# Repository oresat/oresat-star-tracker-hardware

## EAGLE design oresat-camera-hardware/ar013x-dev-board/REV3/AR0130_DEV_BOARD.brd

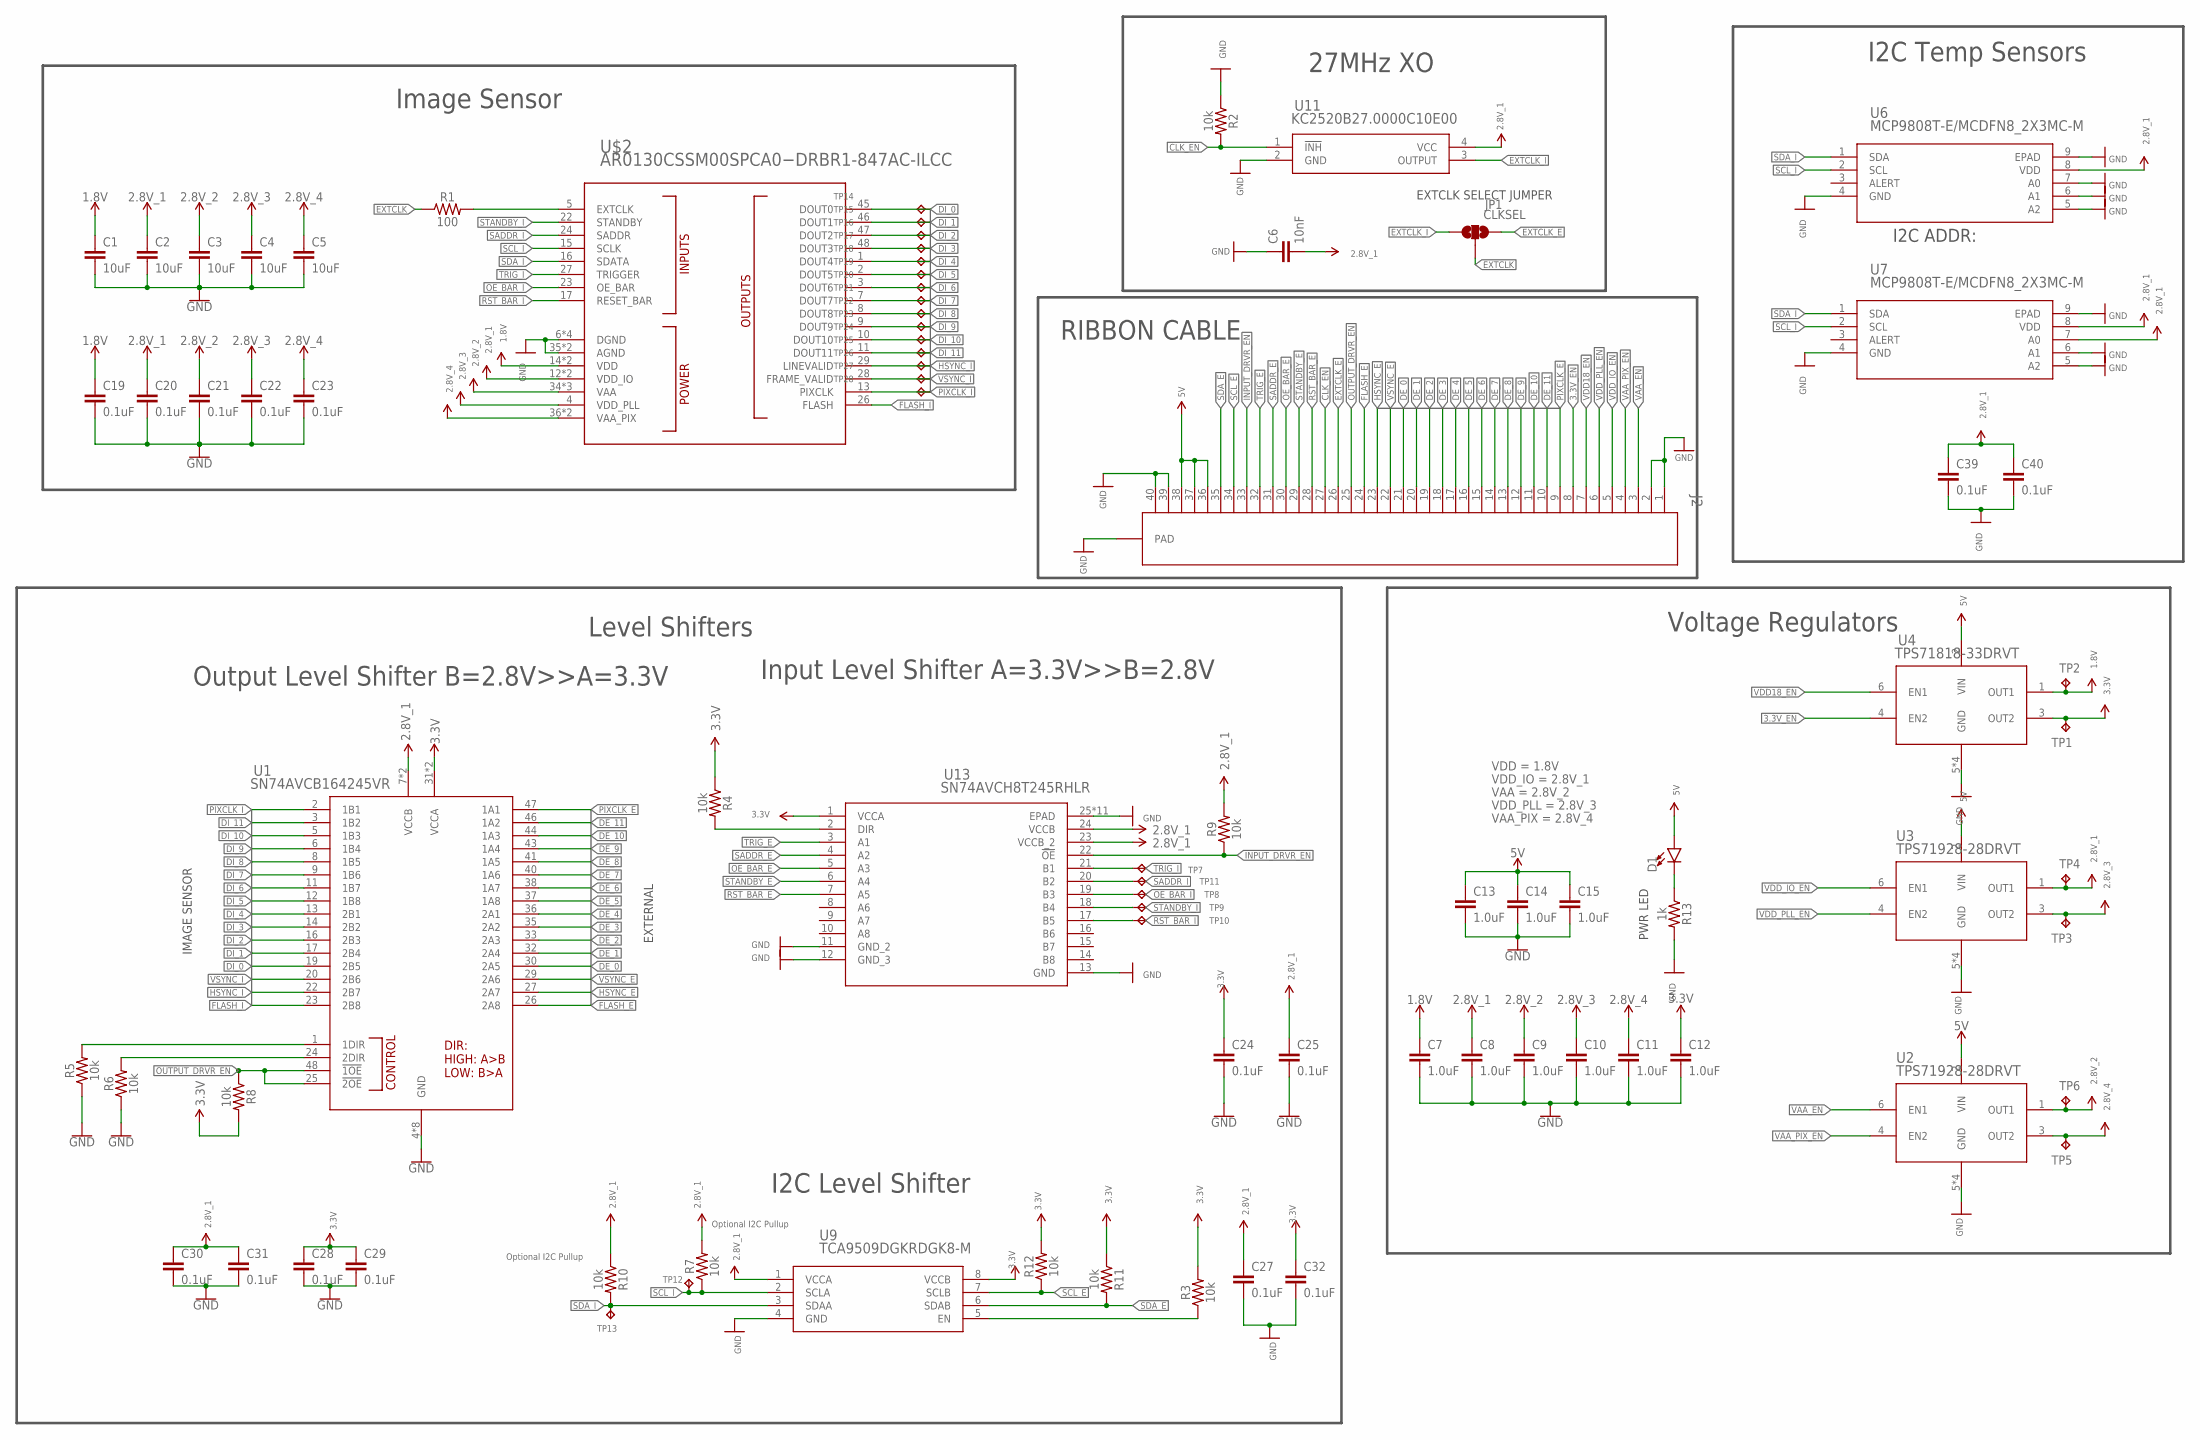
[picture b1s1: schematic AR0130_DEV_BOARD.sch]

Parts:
C1, C2, C3, C4, C5: 10uF; 0603
C6: 10nF; 0402
C7, C8, C9, C10, C11, C12, C13, C14, C15: 1.0uF; 0402
C19, C20, C21, C22, C23, C24, C25, C27, C28, C29, C30, C31, C32, C39, C40: 0.1uF; 0402
D1: LED0603; LED-0603
J2: 4-1734592-04-1734592-0; TE_4-1734592-0
JP1: CLKSEL; SJ_3_PASTE1&2
R1: 100; 0402
R2, R3, R4, R5, R6, R7, R8, R9, R10, R11, R12: 10k; 0402
R13: 1k; 0402
TP1, TP2, TP3, TP4, TP5, TP6, TP7, TP8, TP9, TP10, TP11, TP12, TP13, TP14, TP15, TP16, TP17, TP18, TP19, TP20, TP21, TP22, TP23, TP24, TP25, TP26, TP27, TP28: TPTP06R; TP06R
U1: SN74AVCB164245VR; DGV48
U2, U3: TPS71928-28DRVT; DRV6_1P6X1
U4: TPS71818-33DRVT; DRV6_1P6X1
U6, U7: MCP9808T-E/MCDFN8_2X3MC-M; DFN8_2X3MC-M
U9: TCA9509DGKRDGK8-M; DGK8-M
U11: KC2520B27.0000C10E00; OSC_KYOCERA_KC2520B
U13: SN74AVCH8T245RHLR; RHL24_4P05X2P05
U$2: AR0130CSSM00SPCA0−DRBR1-847AC-ILCC; AR0130CSSM00SPCA0−DRBR1-847AB

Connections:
1.8V: C1.1, C7.1, C19.1, TP2.TP, U4.1 (OUT1), U$2.14 (VDD), U$2.19 (VDD); also elsewhere on the board
3.3V: C12.1, C24.1, C28.1, C29.1, C32.1, R3.2, R4.1, R8.2, R11.1, R12.2, TP1.TP, U1.31 (VCCA), U4.3 (OUT2), U9.8 (VCCB), U13.1 (VCCA); also elsewhere on the board
3.3V_EN: J2.8, U4.4 (EN2); also elsewhere on the board
5V: C13.1, C14.1, C15.1, D1.A, J2.36, J2.37, J2.38, U2.2 (VIN), U3.2 (VIN), U4.2 (VIN); also elsewhere on the board
CLK_EN: J2.27, R2.2, U11.1 (!INH)
DE_0: J2.21, U1.30 (2A5); also elsewhere on the board
DE_1: J2.20, U1.32 (2A4); also elsewhere on the board
DE_2: J2.19, U1.33 (2A3); also elsewhere on the board
DE_3: J2.18, U1.35 (2A2); also elsewhere on the board
DE_4: J2.17, U1.36 (2A1); also elsewhere on the board
DE_5: J2.16, U1.37 (1A8); also elsewhere on the board
DE_6: J2.15, U1.38 (1A7); also elsewhere on the board
DE_7: J2.14, U1.40 (1A6); also elsewhere on the board
DE_8: J2.13, U1.41 (1A5); also elsewhere on the board
DE_9: J2.12, U1.43 (1A4); also elsewhere on the board
DE_10: J2.11, U1.44 (1A3); also elsewhere on the board
DE_11: J2.10, U1.46 (1A2); also elsewhere on the board
DI_0: TP14.TP, U1.19 (2B5), U$2.45 (DOUT0); also elsewhere on the board
DI_1: TP15.TP, U1.17 (2B4), U$2.46 (DOUT1); also elsewhere on the board
DI_2: TP16.TP, U1.16 (2B3), U$2.47 (DOUT2); also elsewhere on the board
DI_3: TP17.TP, U1.14 (2B2), U$2.48 (DOUT3); also elsewhere on the board
DI_4: TP18.TP, U1.13 (2B1), U$2.1 (DOUT4); also elsewhere on the board
DI_5: TP19.TP, U1.12 (1B8), U$2.2 (DOUT5); also elsewhere on the board
DI_6: TP20.TP, U1.11 (1B7), U$2.3 (DOUT6); also elsewhere on the board
DI_7: TP21.TP, U1.9 (1B6), U$2.7 (DOUT7); also elsewhere on the board
DI_8: TP22.TP, U1.8 (1B5), U$2.8 (DOUT8); also elsewhere on the board
DI_9: TP23.TP, U1.6 (1B4), U$2.9 (DOUT9); also elsewhere on the board
DI_10: TP24.TP, U1.5 (1B3), U$2.10 (DOUT10); also elsewhere on the board
DI_11: TP25.TP, U1.3 (1B2), U$2.11 (DOUT11); also elsewhere on the board
EXTCLK: JP1.2, R1.1
EXTCLK_E: J2.26, JP1.3
EXTCLK_I: JP1.1, U11.3 (OUTPUT)
FLASH_E: J2.24, U1.26 (2A8); also elsewhere on the board
FLASH_I: U1.23 (2B8), U$2.26 (FLASH); also elsewhere on the board
HSYNC_E: J2.23, U1.27 (2A7); also elsewhere on the board
HSYNC_I: TP26.TP, U1.22 (2B7), U$2.29 (LINEVALID); also elsewhere on the board
INPUT_DRVR_EN: J2.33, R9.1, U13.22 (!OE)
unnamed: R1.2, U$2.5 (EXTCLK)
unnamed: D1.C, R13.1
unnamed 39: R5.2, U1.1 (1DIR); also elsewhere on the board
unnamed: R3.1, U9.5 (EN)
unnamed: R4.2, U13.2 (DIR)
unnamed 42: R6.2, U1.24 (2DIR); also elsewhere on the board
OE_BAR_E: J2.30, U13.5 (A3)
OE_BAR_I: TP8.TP, U13.19 (B3), U$2.23 (OE_BAR)
OUTPUT_DRVR_EN: J2.25, R8.1, U1.25 (!2OE), U1.48 (!1OE); also elsewhere on the board
PIXCLK_E: J2.9, U1.47 (1A1); also elsewhere on the board
PIXCLK_I: TP28.TP, U1.2 (1B1), U$2.13 (PIXCLK); also elsewhere on the board
RST_BAR_E: J2.28, U13.7 (A5)
RST_BAR_I: TP9.TP, U13.17 (B5), U$2.17 (RESET_BAR)
SADDR_E: J2.31, U13.4 (A2)
SADDR_I: TP11.TP, U13.20 (B2), U$2.24 (SADDR)
SCL_E: J2.34, R12.1, U9.7 (SCLB)
SCL_I: R7.1, TP12.TP, U6.2 (SCL), U7.2 (SCL), U9.2 (SCLA), U$2.15 (SCLK)
SDA_E: J2.35, R11.2, U9.6 (SDAB)
SDA_I: R10.2, TP13.TP, U6.1 (SDA), U7.1 (SDA), U9.3 (SDAA), U$2.16 (SDATA)
STANDBY_E: J2.29, U13.6 (A4)
STANDBY_I: TP10.TP, U13.18 (B4), U$2.22 (STANDBY)
TRIG_E: J2.32, U13.3 (A1)
TRIG_I: TP7.TP, U13.21 (B1), U$2.27 (TRIGGER)
VAA_EN: J2.3, U2.6 (EN1); also elsewhere on the board
VAA_PIX_EN: J2.4, U2.4 (EN2); also elsewhere on the board
VCC: C3.1, C9.1, C21.1, TP6.TP, U2.1 (OUT1), U$2.34 (VAA), U$2.38 (VAA), U$2.40 (VAA); also elsewhere on the board
VCC_1: C4.1, C10.1, C22.1, TP3.TP, U3.3 (OUT2), U$2.4 (VDD_PLL); also elsewhere on the board
VCC_2: C5.1, C11.1, C23.1, TP5.TP, U2.3 (OUT2), U$2.36 (VAA_PIX), U$2.37 (VAA_PIX); also elsewhere on the board
VDD18_EN: J2.7, U4.6 (EN1); also elsewhere on the board
VDD_IO_EN: J2.5, U3.6 (EN1); also elsewhere on the board
VDD_PLL_EN: J2.6, U3.4 (EN2); also elsewhere on the board
VSYNC_E: J2.22, U1.29 (2A6); also elsewhere on the board
VSYNC_I: TP27.TP, U1.20 (2B6), U$2.28 (FRAME_VALID); also elsewhere on the board

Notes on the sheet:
I2C Temp Sensors
I2C Level Shifter
Voltage Regulators
Image Sensor
Output Level Shifter B=2.8V>>A=3.3V
27MHz XO
Input Level Shifter A=3.3V>>B=2.8V
Level Shifters
VDD_IO = 2.8V_1
Optional I2C Pullup
VDD = 1.8V
VDD_PLL = 2.8V_3
VAA = 2.8V_2
VAA_PIX = 2.8V_4
EXTCLK SELECT JUMPER
RIBBON CABLE
IMAGE SENSOR
EXTERNAL
PWR LED
I2C ADDR:

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
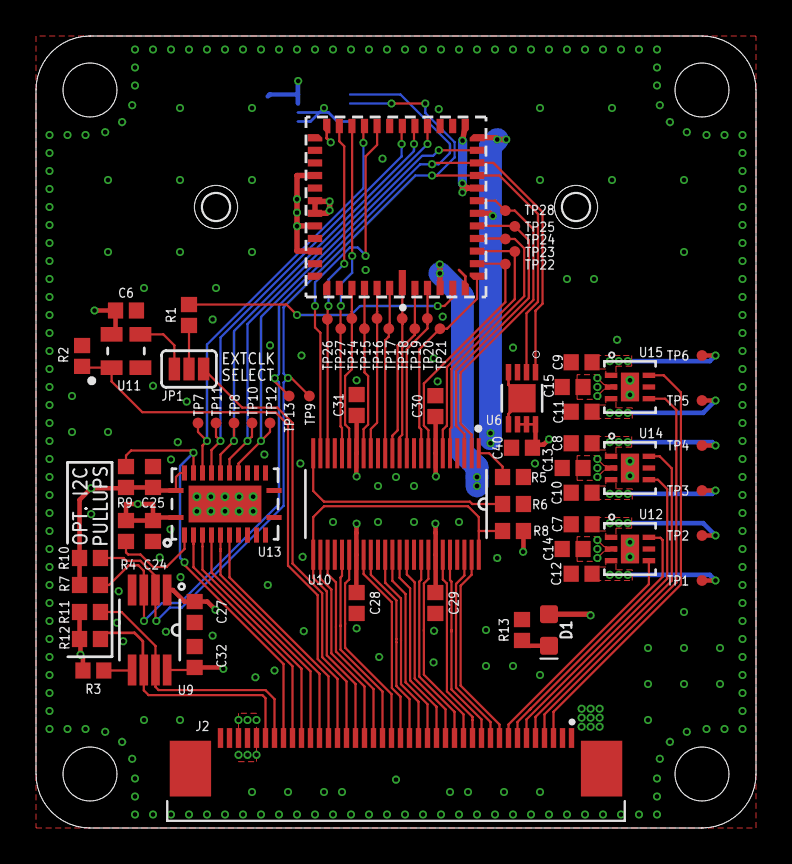
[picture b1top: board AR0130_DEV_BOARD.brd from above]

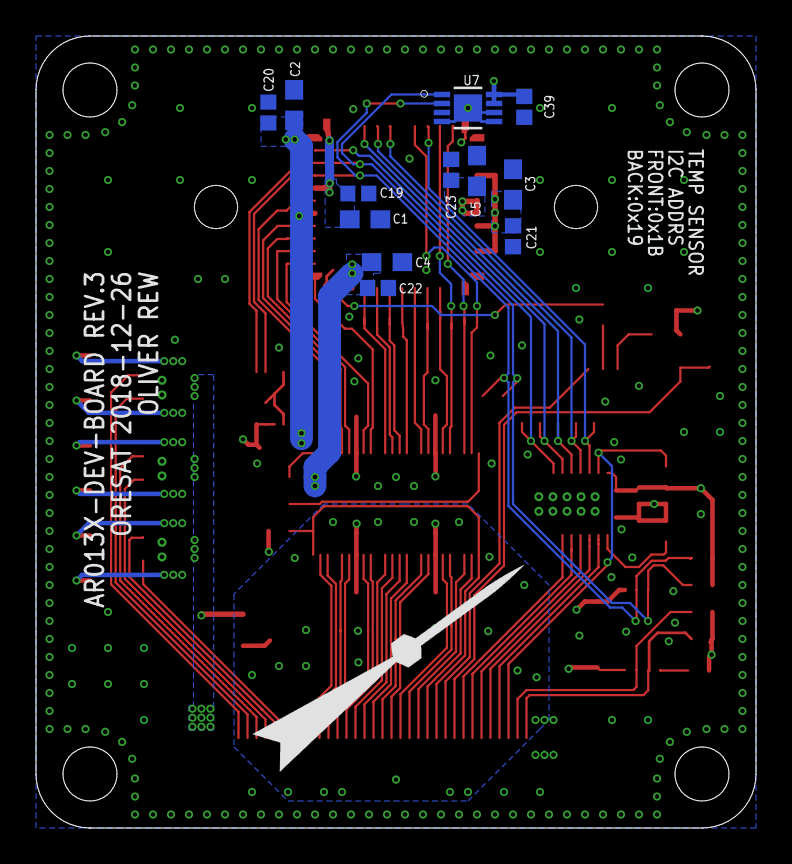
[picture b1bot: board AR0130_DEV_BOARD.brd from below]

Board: 4 copper layers, 40.0 x 44.0 mm, 86 parts (13 on the bottom side), 72 nets.

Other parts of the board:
U10: SN74AVCB164245VR; DGV48
U12: TPS71818-33DRVT; DRV6_1P6X1
U14, U15: TPS71928-28DRVT; DRV6_1P6X1
U$1: M12-LENS-MOUNT
U$3: PSAS_LOGO_15X15

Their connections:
1.8V: U12.1; also elsewhere on the board
3.3V: U10.31, U10.42, U12.3; also elsewhere on the board
3.3V_EN: U12.4; also elsewhere on the board
5V: U12.2, U14.2, U15.2; also elsewhere on the board
DE_0: U10.30; also elsewhere on the board
DE_1: U10.32; also elsewhere on the board
DE_2: U10.33; also elsewhere on the board
DE_3: U10.35; also elsewhere on the board
DE_4: U10.36; also elsewhere on the board
DE_5: U10.37; also elsewhere on the board
DE_6: U10.38; also elsewhere on the board
DE_7: U10.40; also elsewhere on the board
DE_8: U10.41; also elsewhere on the board
DE_9: U10.43; also elsewhere on the board
DE_10: U10.44; also elsewhere on the board
DE_11: U10.46; also elsewhere on the board
DI_0: U10.19; also elsewhere on the board
DI_1: U10.17; also elsewhere on the board
DI_2: U10.16; also elsewhere on the board
DI_3: U10.14; also elsewhere on the board
DI_4: U10.13; also elsewhere on the board
DI_5: U10.12; also elsewhere on the board
DI_6: U10.11; also elsewhere on the board
DI_7: U10.9; also elsewhere on the board
DI_8: U10.8; also elsewhere on the board
DI_9: U10.6; also elsewhere on the board
DI_10: U10.5; also elsewhere on the board
DI_11: U10.3; also elsewhere on the board
FLASH_E: U10.26; also elsewhere on the board
FLASH_I: U10.23; also elsewhere on the board
HSYNC_E: U10.27; also elsewhere on the board
HSYNC_I: U10.22; also elsewhere on the board
unnamed 39: U10.1; also elsewhere on the board
unnamed 42: U10.24; also elsewhere on the board
OUTPUT_DRVR_EN: U10.25, U10.48; also elsewhere on the board
PIXCLK_E: U10.47; also elsewhere on the board
PIXCLK_I: U10.2; also elsewhere on the board
VAA_EN: U15.6; also elsewhere on the board
VAA_PIX_EN: U15.4; also elsewhere on the board
VCC: U15.1; also elsewhere on the board
VCC_1: U14.3; also elsewhere on the board
VCC_2: U15.3; also elsewhere on the board
VDD18_EN: U12.6; also elsewhere on the board
VDD_IO_EN: U14.6; also elsewhere on the board
VDD_PLL_EN: U14.4; also elsewhere on the board
VSYNC_E: U10.29; also elsewhere on the board
VSYNC_I: U10.20; also elsewhere on the board

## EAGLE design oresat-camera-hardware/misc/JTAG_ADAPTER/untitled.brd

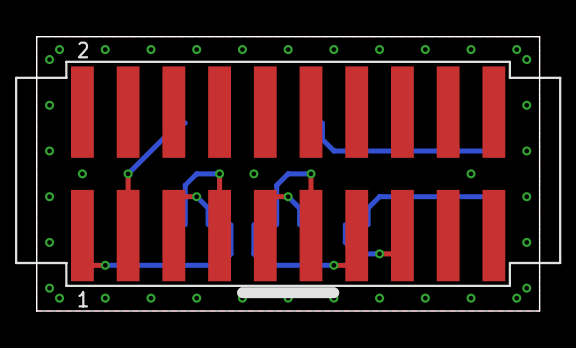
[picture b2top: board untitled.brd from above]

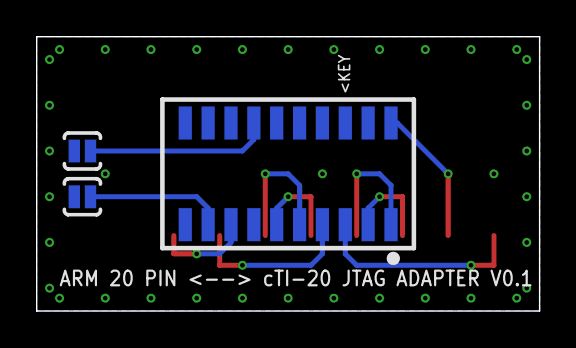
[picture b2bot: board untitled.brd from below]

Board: 2 copper layers, 27.9 x 15.2 mm, 4 parts (3 on the bottom side), 11 nets.

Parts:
J1: RSM-110-02-X-D-LC.LBR
J2: HTST-110-01-XX-DV.LBR
SJ1, SJ2: SOLDERJUMPERNO; SJ_2S-NO

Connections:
EMU1: J1.14, SJ1.1
EMU2: J1.17, SJ2.1
GND: J1.4, J1.8, J1.10, J1.12, J1.16, J1.20, J2.4, J2.6, J2.8, J2.10, J2.12, J2.14, J2.16, J2.18, J2.20, SJ1.2, SJ2.2
NSRST: J1.15, J2.15
NTRST: J1.2, J2.3
RTCK: J1.9, J2.11
TCK: J1.11, J2.9
TDI: J1.3, J2.5
TDO: J1.7, J2.13
TMS: J1.1, J2.7
VTREF: J1.5, J2.1

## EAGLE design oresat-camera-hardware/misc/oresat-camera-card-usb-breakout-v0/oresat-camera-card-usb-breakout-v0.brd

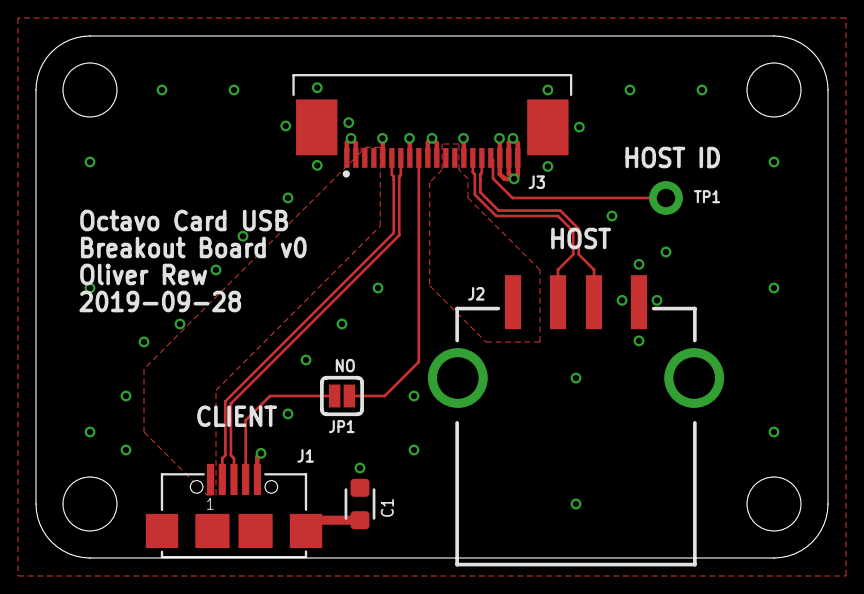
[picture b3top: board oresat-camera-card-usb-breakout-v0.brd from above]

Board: 2 copper layers, 44.0 x 29.0 mm, 6 parts (0 on the bottom side), 11 nets.

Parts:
C1: 100nf; .0603-A
J1: 629105136821
J2: USB_A_SMT_FEMALE; USB-A-S-SILK-FEMALE
J3: 2-1734592-0; TE_2-1734592-0
JP1: JUMPER-SMT_2_NO_SILK; SMT-JUMPER_2_NO_SILK
TP1: TEST-POINTPOGO_PTH; 1X01_NO_SILK

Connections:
CLIENT_VBUS: J1.1, J3.3, J3.4
GND: C1.1, J1.5, J2.GND, J2.SHLD1, J2.SHLD2, J3.1, J3.2, J3.5, J3.8, J3.10, J3.11, J3.14, J3.18, J3.19, J3.20, J3.S1, J3.S2
HOST_VBUS: J2.VBUS, J3.12, J3.13
unnamed: C1.2, J1.SHELL, J1.SHELL1, J1.SHELL2, J1.SHELL3
unnamed: J3.17, TP1.1
unnamed: J1.4, JP1.2
unnamed: J3.9, JP1.1
USB_C_N: J1.2, J3.6
USB_C_P: J1.3, J3.7
USB_H_N: J2.D-, J3.15
USB_H_P: J2.D+, J3.16

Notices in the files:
parts and their libraries:
SparkFun-Resistors: Licensing: Creative Commons ShareAlike 4.0 International - https://creativecommons.org/licenses/by-sa/4.0
SparkFun-Passives: Licensing: CC v3.0 Share-Alike You are welcome to use this library for commercial purposes.
